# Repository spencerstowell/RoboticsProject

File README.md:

# RRT Path Planning - BYU ME-537 Robotics Project
This repository contains my libraries and code for a Robotics class Final Project I completed with a classmate, Ryan Hall. We implemented a unique form of Rapidly Exploring Random Trees (RRT) to plan a path for a robot arm. The unique nature of my RRT algorithm involved the method we used to generate each node in my tree. Rather than generating a random point in space and attaching to the nearest neighbor, we selected a parent node first and propagated in a random direction from there.

Tunable parameters in this code include:
  - Magnitude of bias towards the goal
  - Number of children nodes to generate for each parent
  - Step size
  - Placement and size of obstacles

After the RRT algorithm has identified a viable path from start-finish that successfully navigates the obstacles, a simple path-smoothing algorithm attempts to cut out intermediate nodes by searching for "line-of-sight" between different nodes on the path. The final path is then converted into a series of points, which are fed into an IK controller (Damped-Psuedo Inverse method) that models the behavior of a small robot arm tracing the path.

Strengths of this algorithm:
  - This RRT method is able to iterate extremely quickly because each parent node is known prior to the creation of a new node. This eliminates the need to search through the existing tree when each node is created
  - The line-of-sight smoothing method is also very fast since it only looks at the history of nodes associated with the final path.

Weaknesses of this algorithm:
  - The known-parent approach results in a high point density at the start and low density at the end. This means that the number of points required to obtain a path increases exponentially with decreasing step size.
  - The blocks of code that check for interence with obstacles do not consider the behavior of the robot arm. T,his enables greater speed in the algorithm, but only guarantees the end effector will avoid the obstacles. The IK control similarly does not take obstacle placement into account, nor does it check for self-interference.
  - The path smoothing algorithm only analyzes points on the final path, and does not attempt to minimize the travel distance of the end effector by searching through the entire set of points in the tree.
 
In addition to the Python code, there are some Arduino files for running multiple steppers with non-blocking code. The original intent was to set up an Arduino Nano to function as a ROS node via Rosserial (ROS1), which would then accept joint angles generated by the IK function. However, the project did not progress beyond simulation based on time constraints with the end of the semester. However, there are some Eagle PCB files that present the schematic and board layout for the Arduino Nano and stepper motors.

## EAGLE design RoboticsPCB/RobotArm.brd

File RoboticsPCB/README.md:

# Overview
This folder contains the Autodesk EAGLE board (.brd) and schematic (.sch) files I created to assist with the hardware side of the robot we simulated for RRT.

The stepper motor drivers we used were the [ULN2003A](https://en.wikipedia.org/wiki/ULN2003A) with the [28BYJ](https://lastminuteengineers.com/28byj48-stepper-motor-arduino-tutorial/) stepper motor.

I personally milled the pcb on my desktop CNC machine, a Genmitsu 3018PRO, using the .grbl files in the [useful](/RoboticsPCB/useful/) directory. I converted the files to .gcode via [Flatcam](http://flatcam.org/manual/introduction.html) and used a 30° drill bit to isolate the traces.

## Soldered Board w/ Milled Traces

## Fully Populated Board

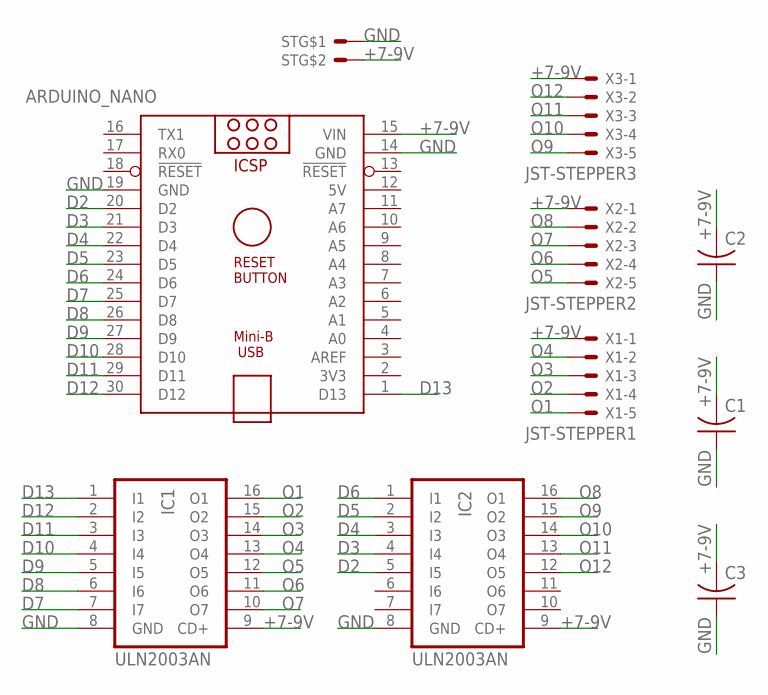
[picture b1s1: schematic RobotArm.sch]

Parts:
ARDUINO_NANO: ARDUINO_NANO
C1, C2, C3: C-US050-024X044; C050-024X044
IC1, IC2: ULN2003AN; DIL16
ST: SCREWTERMINAL2.54; 2.54MM
X1: JST-STEPPER1; JST-XH-05-PACKAGE-LONG-PAD
X2: JST-STEPPER2; JST-XH-05-PACKAGE-LONG-PAD
X3: JST-STEPPER3; JST-XH-05-PACKAGE-LONG-PAD

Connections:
5V: ARDUINO_NANO.12 (5V)
+7-9V: ARDUINO_NANO.15 (VIN), C1.2, C2.2, C3.2, IC1.9 (CD+), IC2.9 (CD+), ST.P$2, X1.1, X2.1, X3.1
D2: ARDUINO_NANO.20 (D2), IC2.5 (I5)
D3: ARDUINO_NANO.21 (D3), IC2.4 (I4)
D4: ARDUINO_NANO.22 (D4), IC2.3 (I3)
D5: ARDUINO_NANO.23 (D5), IC2.2 (I2)
D6: ARDUINO_NANO.24 (D6), IC2.1 (I1)
D7: ARDUINO_NANO.25 (D7), IC1.7 (I7)
D8: ARDUINO_NANO.26 (D8), IC1.6 (I6)
D9: ARDUINO_NANO.27 (D9), IC1.5 (I5)
D10: ARDUINO_NANO.28 (D10), IC1.4 (I4)
D11: ARDUINO_NANO.29 (D11), IC1.3 (I3)
D12: ARDUINO_NANO.30 (D12), IC1.2 (I2)
D13: ARDUINO_NANO.1 (D13), IC1.1 (I1)
GND: ARDUINO_NANO.14 (GND), ARDUINO_NANO.19 (GND), C1.1, C2.1, C3.1, IC1.8 (GND), IC2.8 (GND), ST.P$1
O1: IC1.16 (O1), X1.5
O2: IC1.15 (O2), X1.4
O3: IC1.14 (O3), X1.3
O4: IC1.13 (O4), X1.2
O5: IC1.12 (O5), X2.5
O6: IC1.11 (O6), X2.4
O7: IC1.10 (O7), X2.3
O8: IC2.16 (O1), X2.2
O9: IC2.15 (O2), X3.5
O10: IC2.14 (O3), X3.4
O11: IC2.13 (O4), X3.3
O12: IC2.12 (O5), X3.2

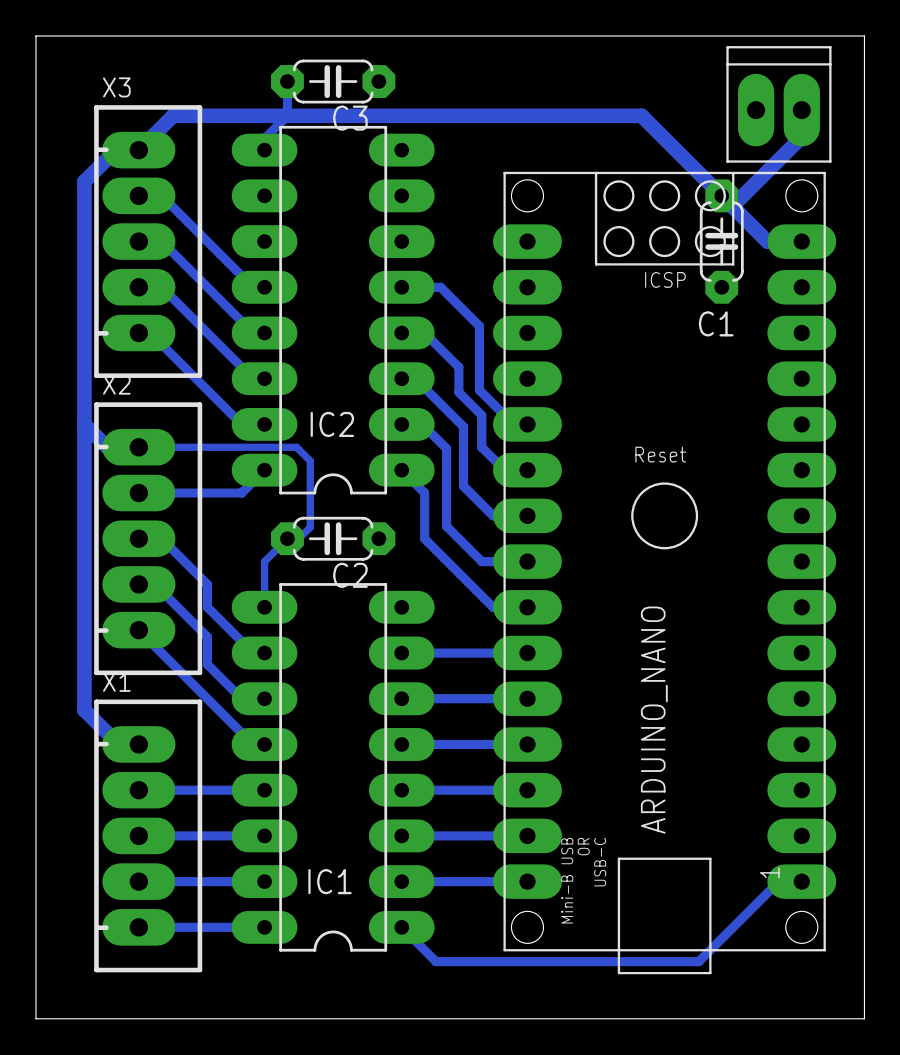
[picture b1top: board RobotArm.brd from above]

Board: 2 copper layers, 46.0 x 54.6 mm, 10 parts (0 on the bottom side), 26 nets.

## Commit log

2023-11-23 Added ROS node python file
2023-11-23 Initial code written with copilot
2023-11-26 Added nano_code.ino and modified InputCode.py
2023-11-26 Added file for non-blocking arduino code
2023-11-27 Updated Stepper_Control.ino
2023-11-28 Clarified in_obstacle fn and added init parameters
2023-11-29 Testing for negative angles in 'new' movement fns
2023-11-29 Fixed negative signs
2023-12-03 Checking for workspace limits
2023-12-03 Added additional RRT fn's
2023-12-05 Added RRT fn's & changed filename
2023-12-06 Class files added + basic RRT
2023-12-07 Optimized RRT to use 'leaf' nodes & smoothing fn
2023-12-11 Added in the following: IK code to find joint positions, Interpolation to get a smoother path. Visualization of joints and Robot arm visuaization.
2023-12-11 working through the interpolation of code -R
2023-12-11 forgot to save
2023-12-12 Minor updates to RRT algorithm
2023-12-12 Fixed controller to use pinv instead of J_T and updated interpolation
2023-12-12 Added obstacle to prevent self-interference workspace
2023-12-12 Added some proof of completion
2023-12-12 wouldnt let me swap?
2023-12-12 Sim changes
2023-12-12 Attempted Nano/Pyserial
2024-01-29 Added additional images of the solver
2024-01-29 Cleaned out unused blocks of code for final commit
2024-01-29 Fixed unneeded print statements
2024-01-29 Added Eagle PCB & Schematic files
2024-01-29 Added PCB pictures
2024-01-29 Resized images
2024-01-29 Updated Folder name
